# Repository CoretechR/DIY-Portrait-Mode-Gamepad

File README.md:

# DIY Portrait-Mode Gamepad

<div align="center">
  
</div>

## Overview

This RP2040-powered gamepad is designed for portrait-mode games. It plugs directly into a smartphone's USB-C port and is compatible with virtually any operating system. No Bluetooth connection or batteries are required as the gamepad communicates directly via USB and acts as a HID controller. The button layout is ideal for emulators, but the side buttons also enable landscape-mode gaming. The gamepad uses the fantasic [GP2040-CE](https://github.com/OpenStickCommunity/GP2040-CE) firmware, which also enables a local webserver Web-UI for configuration. Finally, all parts of the case and buttons are fully 3D-printable. 

<div align="center">
  
</div>

### Features
* Small form factor
* Portrait-Mode gaming
* USB-Powered - no battery needed
* Made for the GP2040-CE firmware

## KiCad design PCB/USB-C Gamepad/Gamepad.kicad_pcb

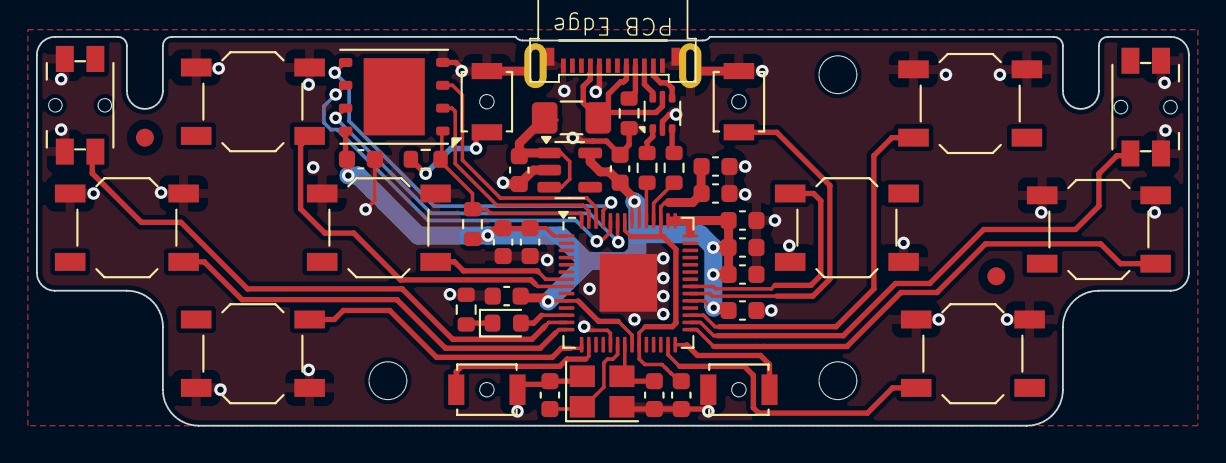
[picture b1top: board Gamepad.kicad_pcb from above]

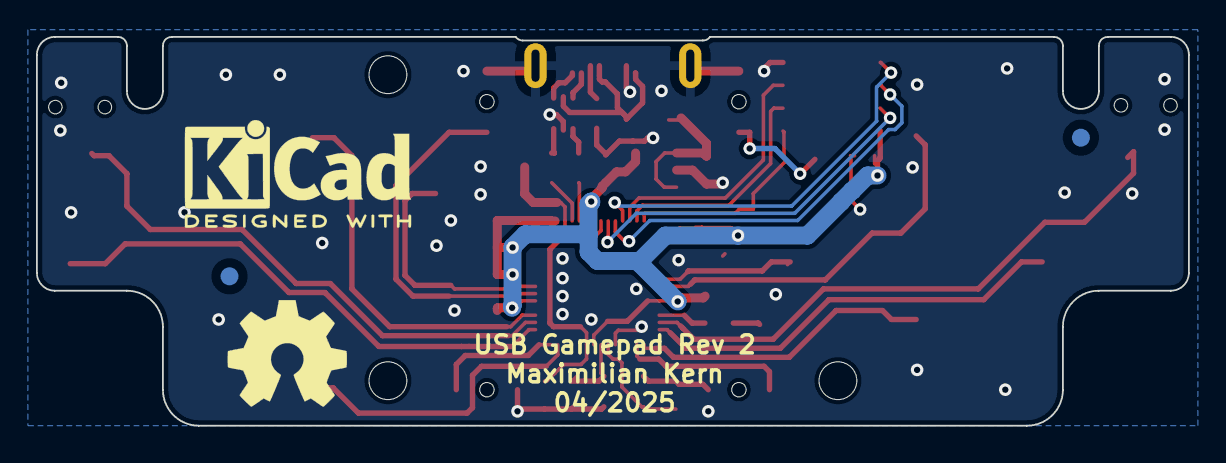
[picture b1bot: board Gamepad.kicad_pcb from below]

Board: 2 copper layers, 64.0 x 21.6 mm, 50 parts (2 on the bottom side), 36 nets.

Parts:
C1, C2, C3, C11, C13: 1uF; C_0603_1608Metric
C4, C7, C8, C9, C10, C12, C14, C15: 100nF; C_0603_1608Metric
C5, C6: 15pF; C_0603_1608Metric
D1: LED; LED_0603_1608Metric
F1: 500mA; Fuse_1206_3216Metric_Pad1.42x1.75mm_HandSolder
FID1, FID2, FID3, FID4: Fiducial; Fiducial_1mm_Mask2mm
H1, H2, H3: MountingHole; MountingHole_2.1mm
J1: USB_C_Receptacle_USB2.0; USB_TYPEC_PLUG_12P
R1: 10k; R_0603_1608Metric
R2: 1k; R_0603_1608Metric
R3, R4: 27; R_0603_1608Metric
R5: 2k2; R_0603_1608Metric
R7: 5.1k; R_0603_1608Metric
SW1, SW2, SW3, SW4, SW6, SW7, SW8, SW9: SW_Push; SW_SPST_TL3342
SW5, SW10: SW_Push; Panasonic_EVQPUM_EVQPUD
SW11, SW12, SW13, SW14: SW_Push; SW_SPST_B3U-1000P-B
U1: AP2112K-3.3; SOT-23-5
U2: USBLC6-2P6; SOT-666
U3: W25Q64JVZPIQ; WSON-8-1EP_6x5mm_P1.27mm_EP3.4x4.3mm
U4: RP2040; QFN-56-1EP_7x7mm_P0.4mm_EP3.2x3.2mm
Y1: ABM8-272-T3; Crystal_SMD_Abracon_ABM8G-4Pin_3.2x2.5mm

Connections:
+1V1: C11.1, C14.1, C15.1, U4.23 (DVDD), U4.45 (VREG_VOUT), U4.50 (DVDD)
+3.3V: C2.1, C3.1, C4.1, C7.1, C8.1, C9.1, C10.1, C12.1, C13.1, R1.1, U1.5 (VOUT), U3.8 (VCC), U4.1 (IOVDD), U4.10 (IOVDD), U4.22 (IOVDD), U4.33 (IOVDD), U4.42 (IOVDD), U4.43 (ADC_AVDD), U4.44 (VREG_IN), U4.48 (USB_VDD), U4.49 (IOVDD)
/BT_A1: R2.2, SW13.1
/BT_A2: SW14.1, U4.34 (GPIO22)
/BT_B1: SW9.1, U4.27 (GPIO16)
/BT_B2: SW8.1, U4.29 (GPIO18)
/BT_B3: SW7.1, U4.35 (GPIO23)
/BT_B4: SW6.1, U4.31 (GPIO20)
/BT_Down: SW3.1, U4.15 (GPIO12)
/BT_L1: SW5.2, U4.13 (GPIO10)
/BT_Left: SW2.1, U4.14 (GPIO11)
/BT_R1: SW10.2, U4.30 (GPIO19)
/BT_Right: SW4.1, U4.7 (GPIO5)
/BT_S1: SW11.1, U4.16 (GPIO13)
/BT_S2: SW12.1, U4.28 (GPIO17)
/BT_Up: SW1.1, U4.8 (GPIO6)
/D_N: J1.A7 (D-), U2.4 (I/O2)
/D_P: J1.A6 (D+), U2.6 (I/O1)
/USB_D2_N: R4.1, U4.46 (USB_DM)
/USB_D2_P: R3.1, U4.47 (USB_DP)
/VUSB_RAW: F1.1, J1.A4 (VBUS), J1.B9 (VBUS), U2.5 (VBUS)
GND: C1.2, C2.2, C3.2, C4.2, C5.2, C6.1, C7.2, C8.2, C9.2, C10.2, C11.2, C12.2, C13.2, C14.2, C15.2, J1.A1 (GND), J1.A12 (GND), J1.B12 (GND), J1.S1 (SHIELD), R5.1, R7.1, SW1.2, SW2.2, SW3.2, SW4.2, SW5.1, SW6.2, SW7.2, SW8.2, SW9.2, SW10.1, SW11.2, SW12.2, SW13.2, SW14.2, U1.2 (GND), U2.2 (GND), U3.4 (GND), U4.19 (TESTEN), U4.57 (GND), Y1.2, Y1.4
unnamed: D1.2 (A), U4.12 (GPIO9)
unnamed: D1.1 (K), R5.2
unnamed: J1.A5 (CC), R7.2
unnamed: C1.1, F1.2, U1.1 (VIN), U1.3 (EN)
unnamed: C5.1, U4.20 (XIN), Y1.1
unnamed: C6.2, U4.21 (XOUT), Y1.3
QSPI_CS: R1.2, R2.1, U3.1 (~CS), U4.56 (QSPI_SS)
QSPI_SCLK: U3.6 (CLK), U4.52 (QSPI_SCLK)
QSPI_SD0: U3.5 (DI(IO0)), U4.53 (QSPI_SD0)
QSPI_SD1: U3.2 (DO(IO1)), U4.55 (QSPI_SD1)
QSPI_SD2: U3.3 (IO2), U4.54 (QSPI_SD2)
QSPI_SD3: U3.7 (IO3), U4.51 (QSPI_SD3)
USB_D_N: R4.2, U2.3 (I/O2)
USB_D_P: R3.2, U2.1 (I/O1)

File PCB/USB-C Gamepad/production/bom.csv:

Designator,Footprint,Quantity,Value,LCSC Part #
"C1, C11, C13, C2, C3",0603,5,1uF,C15849
"C10, C12, C14, C15, C4, C7, C8, C9",0603,8,100nF,C1591
"C5, C6",0603,2,15pF,C107037
D1,0603,1,LED,C965807
F1,1206,1,500mA,C220146
J1,USB_TYPEC_PLUG_12P,1,USB_C_Receptacle_USB2.0,C2879827
R2,0603,1,1k,C22548
"R3, R4",0603,2,27,C137753
R5,0603,1,2k2,C114662
R7,0603,1,5.1k,C105580
"SW1, SW2, SW3, SW4, SW6, SW7, SW8, SW9",SW_SPST_TL3342,8,SW_Push,C2762971
"SW10, SW5",Panasonic_EVQPUM_EVQPUD,2,SW_Push, C388642
"SW11, SW12, SW13, SW14",SW_SPST_B3U-1000P-B,4,SW_Push,C231329
U1,SOT-23-5,1,AP2112K-3.3,C51118
U2,SOT-666,1,USBLC6-2P6,C2827693
U3,WSON-8-1EP_6x5mm_P1.27mm_EP3.4x4.3mm,1,W25Q64JVZPIQ,C2940197
U4,QFN-56-1EP_7x7mm_P0.4mm_EP3.2x3.2mm,1,RP2040, C2040
Y1,Crystal_SMD_Abracon_ABM8G-4Pin_3.2x2.5mm,1,ABM8-272-T3,C20625731
